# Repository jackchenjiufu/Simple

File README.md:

# Simple Server / DOO

轻量级 PHP RESTful API 服务框架 — 中间件链 + 服务-仓库分层架构，内置 80+ API、频率限制、RBAC 权限、考勤薪资、自动化爬虫、反馈系统。配套 uni-app（Vue 3）跨端 App 和 Vue 3 / 原生双版本管理后台。

## 架构

```
请求 → CORS 中间件 → 日志中间件 → 错误中间件 → 路由 → 响应
                                                    ↓
                                              Service 层
                                                    ↓
                                            Repository 层
                                                    ↓
                                              PDO / MySQL
```

统一路由入口：`/api/*` 经 `.htaccess` → `index.php` 集中分发（RESTful 路由 + 传统文件路由双模式）。

## 目录

```
server/
├── api/          # 80+ API 接口（认证/用户/内容/社交/文件/考勤/反馈/爬虫/管理后台）
├── config/       # Config.php（.env管理） + Database.php（PDO） + RateLimiter.php（限流）
├── middleware/    # CORS / 日志 / 错误 / 认证 — 链式中间件
├── services/     # UserService / ContentService — 业务逻辑
├── repositories/ # UserRepository / ContentRepository — 数据访问
├── uploads/      # 上传文件
├── downloads/    # APK 下载
├── sql/          # 数据库脚本
├── websocket/    # Node.js WebSocket 推送服务（服务端，App 端未接入）
└── mail.php      # 邮件（PHPMailer）

admin-vue/        # 管理后台（Vue 3 SPA，Hash 路由）
admin-web/        # 管理后台（原生 HTML/JS/CSS，传统版）
admin-vue-dist/   # admin-vue 构建产物

pages/            # uni-app (Vue 3) 前端页面
components/       # Vue 组件库
store/            # Vuex 状态管理
utils/            # 工具函数（请求封装/行为分析/缓存）
websocket/        # App 端 WebSocket 连接逻辑（App.vue 内嵌）
```

## 快速开始

```bash
git clone git@github.com:jackchenjiufu/Simple.git
cd Simple
composer install
cp server/config/.env.example server/config/.env   # 编辑数据库配置
mysql -u root -p < server/sql/doo-app.sql
```

```bash
# 初始化
curl http://localhost/server/api/init_database.php
curl http://localhost/server/api/reset_admin.php        # 重置管理员密码（部署后自行设定，勿用示例值）
```

## API 概览（80+ 接口）

| 模块 | 接口数 | 核心功能 |
|------|--------|----------|
| 认证 | 8 | 登录/注册/改密/忘记密码（频率限制 + 邮件验证码） |
| 用户 | 5 | 用户列表/画像/等级/行为分析 |
| 内容 | 10 | CRUD/轮播图/文章/用户行为同步 |
| 反馈 | 2 | 用户提交反馈 + 查看回复历史 |
| 社交 | 6 | 关注/粉丝/私信/聊天记录 |
| 文件/图片 | 11 | 上传/预览/列表/删除/批量导入/下载代理 |
| 收藏 | 2 | 收藏列表/添加收藏 |
| 考勤薪资 | 2 | 打卡 + 加班费 + 五险一金 + 个税（江苏标准） |
| 公告 | 1 | 公告列表 |
| RBAC | 1 | 4 角色 + 12 权限/动态分配 |
| 爬虫 | 3 | 抖音热榜→自动发文章 / picsum→自动发图 |
| 系统 | 9 | 监控/部署/AI代理/版本管理/数据库初始化 |
| 管理后台 | 12 | 用户/内容/轮播/消息/日志/统计/反馈/权限/开屏/文章管理 |

### WebSocket（服务端）

- `websocket/ws-server.js`：Node.js 推送服务（ws://your-domain.com:1884）
- ⚠️ App 端当前**未接入** WebSocket，私聊走轮询（chat.vue 5s / conversations.vue 10s）

## 响应格式

```json
{ "code": 200, "message": "成功", "data": { ... } }
```

## 安全

- bcrypt 密码哈希 | 全量 PDO 预处理 | 频率限制
- Session + Token 双重认证 | CORS 白名单 | 文件上传白名单 + 大小限制
- Token 认证（64 字符随机 hex） | 错误信息脱敏

## 管理后台

| 版本 | 技术 | 路径 | 状态 |
|------|------|------|------|
| Vue 3 SPA | Vue 3 + Vue Router (Hash) | `admin-vue/` | ✅ 主力版 |
| 原生版 | HTML/JS/CSS 传统多页 | `admin-web/` | ✅ 共存 |

功能：仪表盘 / 用户管理 / 内容管理 / 轮播图 / 公告 / 文章 / 反馈管理 / 开屏配置 / 数据统计 / 操作日志

## 技术栈

**后端**: PHP + MySQL + PDO + PHPMailer + Node.js (WebSocket)  
**前端**: uni-app (Vue 3) + Vite + Capacitor 6 → Android APK  
**后台**: Vue 3 SPA + 原生 HTML/JS/CSS 双版本  
**管理入口**: http://your-domain.com:7070/doo/admin-vue/  
**配置**: `E:/poo/doo/server/config/`

## License

ISC

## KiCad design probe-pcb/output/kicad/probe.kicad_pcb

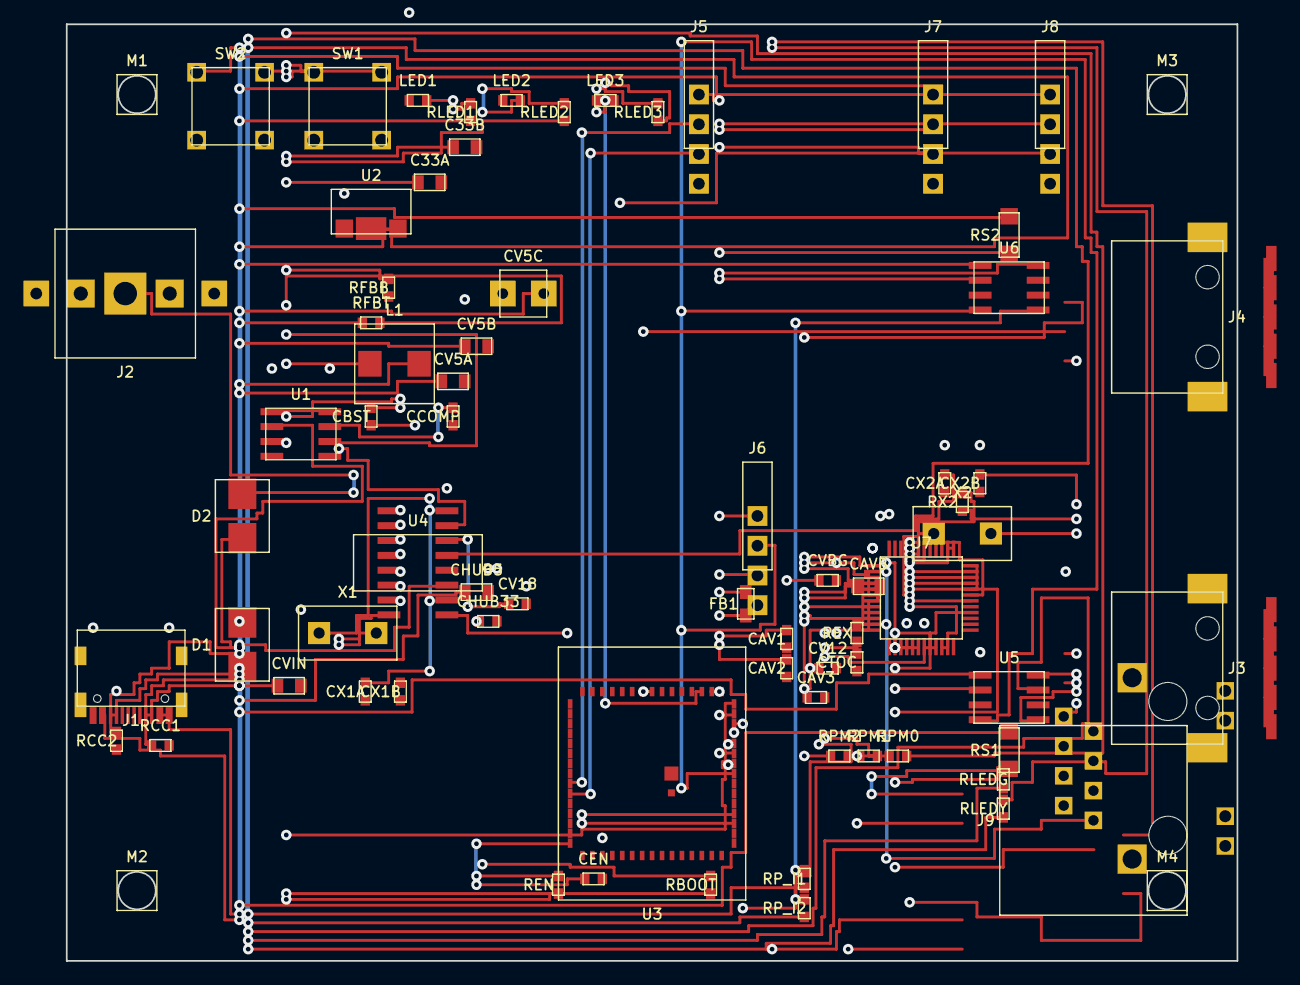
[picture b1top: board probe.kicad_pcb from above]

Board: 2 copper layers, 100.0 x 80.0 mm, 74 parts (0 on the bottom side), 63 nets.

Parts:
C33A: 0805-P; C33A
C33B: 0805-P; C33B
CAV1: 0603-P; CAV1
CAV2: 0603-P; CAV2
CAV3: 0603-P; CAV3
CAVB: 0805-P; CAVB
CBST: 0603-P; CBST
CCOMP: 0603-P; CCOMP
CEN: 0603-P; CEN
CHUB5: 0805-P; CHUB5
CHUB33: 0603-P; CHUB33
CTOC: 0603-P; CTOC
CV5A: 0805-P; CV5A
CV5B: 0805-P; CV5B
CV5C: caprad; CV5C
CV12: 0603-P; CV12
CV18: 0603-P; CV18
CVBG: 0603-P; CVBG
CVIN: 0805-P; CVIN
CX1A: 0603-P; CX1A
CX1B: 0603-P; CX1B
CX2A: 0603-P; CX2A
CX2B: 0603-P; CX2B
D1: SS34; D1
D2: SS34; D2
FB1: FB-0805; FB1
J1: TYPE-C-31-M-12; J1
J2: DC-005; J2
J3: USB3.0-A; J3
J4: USB3.0-A; J4
J5: HDR1x4; J5
J6: HDR1x4; J6
J7: HDR1x4; J7
J8: HDR1x4; J8
J9: HR911105A; J9
L1: 10uH; L1
LED1: LED-0603; LED1
LED2: LED-0603; LED2
LED3: LED-0603; LED3
M1: mount; M1
M2: mount; M2
M3: mount; M3
M4: mount; M4
RBOOT: 0603-P; RBOOT
RCC1: 5.1k; RCC1
RCC2: 5.1k; RCC2
REN: 0603-P; REN
REX: 0603-P; REX
RFBB: 0603-P; RFBB
RFBT: 0603-P; RFBT
RLED1: 0603-P; RLED1
RLED2: 0603-P; RLED2
RLED3: 0603-P; RLED3
RLEDG: 0603-P; RLEDG
RLEDY: 0603-P; RLEDY
RPM0: 0603-P; RPM0
RPM1: 0603-P; RPM1
RPM2: 0603-P; RPM2
RP_I1: 0603-P; RP_I1
RP_I2: 0603-P; RP_I2
RS1: 0.05R; RS1
RS2: 0.05R; RS2
RX2: 0603-P; RX2
SW1: TACT; SW1
SW2: TACT; SW2
U1: MP1584EN; U1
U2: AMS1117-3.3; U2
U3: ESP32-S3-MINI-1; U3
U4: SL2.1A; U4
U5: INA219; U5
U6: INA219; U6
U7: W5500; U7
X1: 12MHz; X1
X2: 25MHz; X2

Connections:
ACTN: J9.10, U7.27
AV33: CAV1.1, CAV2.1, CAV3.1, CAVB.1, FB1.2, U7.4, U7.8, U7.11, U7.15, U7.17, U7.21, U7.28
BOOTN: RBOOT.1, SW2.1, SW2.2, U3.4
BST: CBST.1, U1.1
CC1: J1.A5, RCC1.1
CC2: J1.B5, RCC2.1
COMP: CCOMP.1, U1.7
DC_IN: D2.1, J2.1
ENN: CEN.1, REN.1, SW1.1, SW1.2, U3.45
ETH_RXN: J9.6, U7.5
ETH_RXP: J9.3, U7.6
ETH_TXN: J9.2, U7.1
ETH_TXP: J9.1, U7.2
EXRES: REX.1, U7.10
FB: RFBB.1, RFBT.2, U1.6
GND: C33A.2, C33B.2, CAV1.2, CAV2.2, CAV3.2, CAVB.2, CCOMP.2, CEN.2, CHUB5.2, CHUB33.2, CTOC.2, CV5A.2, CV5B.2, CV5C.-, CV12.2, CV18.2, CVBG.2, CVIN.2, CX1A.2, CX1B.2, CX2A.2, CX2B.2, J1.A1, J1.B1, J1.SH, J2.2, J2.3, J3.4, J3.SH, J4.4, J4.SH, J5.4, J6.4, J7.4, J8.4, J9.SH, LED1.1, RCC1.2, RCC2.2, REX.2, RFBB.2, SW1.3, SW1.4, SW2.3, SW2.4, U1.4, U1.5, U2.1, U3.1, U3.2, U3.42, U3.43, U3.61, U4.12, U5.3, U6.3, U7.3, U7.9, U7.14, U7.16, U7.19, U7.29, U7.48
H1_DM: J3.2, U4.7
H1_DP: J3.3, U4.8
H2_DM: J4.2, U4.5
H2_DP: J4.3, U4.6
H3_DM: J7.2, U4.3
H3_DP: J7.3, U4.4
H4_DM: J8.2, U4.1
H4_DP: J8.3, U4.2
HUB_DM: U3.23, U4.9
HUB_DP: U3.24, U4.10
LED1A: LED1.2, RLED1.1
LED2A: LED2.2, RLED2.1
LED2K: LED2.1, U3.17
LED3A: LED3.2, RLED3.1
LED3K: LED3.1, U3.18
LEDG_A: J9.9, RLEDG.1
LEDY_A: J9.11, RLEDY.1
LINKN: J9.12, U7.25
NC: J1.A6, J1.A7, J1.A8, J1.A9, J1.A12, J1.B6, J1.B7, J1.B8, J1.B9, J1.B12, J2.4, J2.5, J3.5, J3.6, J3.7, J3.8, J3.9, J4.5, J4.6, J4.7, J4.8, J4.9, J9.4, J9.5, J9.7, J9.8, U3.5, U3.6, U3.7, U3.16, U3.19, U3.20, U3.21, U3.22, U3.25, U3.26, U3.27, U3.28, U3.29, U3.30, U3.31, U3.32, U3.33, U3.34, U3.35, U3.36, U3.37, U3.38, U3.41, U3.44, U3.46, U3.47, U3.48, U3.49, U3.50, U3.51, U3.52, U3.53, U3.54, U3.55, U3.56, U3.57, U3.58, U3.59, U3.60, U5.6, U6.6, U7.7, U7.12, U7.13, U7.23, U7.24, U7.26, U7.38, U7.39, U7.40, U7.41, U7.42, U7.46, U7.47
PM0: RPM0.1, U7.45
PM1: RPM1.1, U7.44
PM2: RPM2.1, U7.43
RAW: CVIN.1, D1.2, D2.2, U1.2
RAW_L: D1.1, J1.A4, J1.B4
SCL: J6.2, RP_I1.1, U3.8, U5.4, U6.4
SDA: J6.3, RP_I2.1, U3.9, U5.5, U6.5
SW: CBST.2, L1.1, U1.3
TOCAPN: CTOC.1, U7.20
URX: J5.3, U3.40
UTX: J5.2, U3.39
V5: CHUB5.1, CV5A.1, CV5B.1, CV5C.+, J7.1, J8.1, L1.2, RFBT.1, RLED1.2, RS1.1, RS2.1, U2.3, U4.11, U5.1, U6.1
V12O: CV12.1, U7.22
V18N: CV18.1, U4.14
V33: C33A.1, C33B.1, CHUB33.1, FB1.1, J5.1, J6.1, RBOOT.2, REN.2, RLED2.2, RLED3.2, RLEDG.2, RLEDY.2, RPM0.2, RPM1.2, RPM2.2, RP_I1.2, RP_I2.2, U2.2, U3.3, U4.13, U5.7, U6.7
VBGN: CVBG.1, U7.18
VU1: J3.1, RS1.2, U5.2, U5.8
VU2: J4.1, RS2.2, U6.2, U6.8
W_CS: U3.10, U7.32
W_INT: U3.15, U7.36
W_MISO: U3.13, U7.34
W_MOSI: U3.12, U7.35
W_RST: U3.14, U7.37
W_SCLK: U3.11, U7.33
X1A: CX1A.1, U4.16, X1.1
X1B: CX1B.1, U4.15, X1.2
X2A: CX2A.1, RX2.1, U7.30, X2.1
X2B: CX2B.1, RX2.2, U7.31, X2.2

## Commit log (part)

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2026-06-19 chore: 移除安全审计报告
2026-06-20 add LICENSE.
2026-06-21 fix: 优化文章详情排版、系统设置清理缓存、登录页协议问题、密码重置流程修复
    - 文章详情页排版丰富化，添加封面、作者卡片、标签区、阅读进度
    - 系统设置新增清理缓存功能
    - 登录页移除用户协议复选框（修复无法查看协议问题）
    - 密码重置：邮箱验证码 API 改名绕过 WAF 拦截
    - 修复 PHP 文件 CRLF 换行符导致 404 的问题
    - mail.php 添加 Composer 自动加载 fallback 机制
2026-06-22 v1.2.4: 版本显示修复、密码/重置密码/关于/隐私/协议/设置页面UI统一对齐登录页风格、静默WGT热更新、删除账号功能、检查更新优化
2026-06-22 feat: integrate Getui push notification
    - Add Push module to manifest.json
    - Create push.php API (bind CID / send push)
    - Add push_cid column to users table
    - Initialize push on app launch, auto-bind CID on login
2026-06-22 feat: login auto-bind push CID
2026-06-22 chore: bump to v1.2.5
2026-06-22 feat: push API with Getui integration
2026-06-22 fix: switch to DCloud UniPush API
2026-06-22 fix: WGT热更新改用plus.runtime.install直接传URL下载安装
2026-06-22 Revert "fix: WGT热更新改用plus.runtime.install直接传URL下载安装"
    This reverts commit 758a274cb1e3135793a7abe9cdc422e0af1c9b7e.
2026-06-22 Revert "fix: WGT热更新改用plus.runtime.install直接传URL下载安装"
    This reverts commit a1e476033828624d5a89ebff296d24175be2a5f6.
2026-06-22 v1.2.6: 移除Push模块、修复WGT安装冲突、APK/WGT自动切换、清理硬编码配置
2026-06-23 fix: WebSocket heartbeat 5s, notification API fix
2026-06-23 remove: Getui push integration
2026-06-23 fix: WebSocket reconnect 1s, immediate heartbeat
2026-06-23 fix: use native WebSocket API instead of uni.connectSocket
2026-06-23 fix: simplify WS to uni.connectSocket with heartbeat 10s
2026-06-23 fix: use uni.onSocketOpen/Message/Close global API
2026-06-23 fix: register WS event listeners only once
2026-06-23 fix: WS heartbeat 2s to prevent Android idle timeout
2026-06-23 feat: Node.js WebSocket server (stable replacement for PHP Workerman)
2026-06-23 feat: push API on Node.js WS server
2026-06-23 fix: add Push module back for uni.createPushMessage
2026-06-23 fix: JSON ping/pong heartbeat for uni-app compatibility
2026-06-23 fix: login redirect with no animation to reduce flash
2026-06-23 feat: add splash startup page
2026-06-23 feat: splash config API + admin page
2026-06-23 fix: integrate splash into admin sidebar + script.js
2026-06-23 fix: splash handler in switchMenu
2026-06-27 clean: remove recommend cards, keep carousel only
2026-06-27 fix: syntax error in tabbar-1 methods
2026-06-27 carousel height 300px + adjustable via prop
2026-06-27 carousel default height 300px
2026-06-27 feat: Vue 3 + Element Plus admin backend
2026-06-27 feat: complete admin pages (Announcement/Content/Article/Feedback/Stats/Logs)
2026-06-27 fix: Element Plus icons + axios withCredentials
2026-06-27 fix: admin pages data mapping + session_start fix
2026-06-27 fix: admin pages full data fields + Content/Logs
2026-06-27 feat: add edit/delete for Carousel and Announcement
2026-06-27 feat: Article/Feedback/Dashboard pages + feedback status toggle
2026-06-27 feat: article CRUD + feedback 未读/已读/已解决 + richer dashboard
2026-06-27 feat: user management CRUD (add/edit/delete)
2026-06-27 fix: remove withCredentials (same-origin)
2026-06-27 fix: relative API URL for same-origin
2026-06-27 fix: token-based auth for admin APIs
2026-06-27 fix: auth_helper no body consume + user avatar
2026-06-27 fix: carousel load use GET instead of POST
2026-06-27 fix: delete requests use query params not body
2026-06-27 feat: content CRUD + edit page + dashboard stats
2026-06-27 feat: carousel image upload + user avatar upload
2026-06-27 fix: build errors in carousel upload attributes
2026-06-27 redesign: admin login page (careercompass style)
2026-06-27 redesign: admin-vue login page (careercompass)
2026-06-27 fix: dashboard stats - use real API fields
2026-06-27 fix: live online count from WebSocket server
2026-06-27 feat: feedback history in my-feedback page
2026-06-27 fix: add tab/historyList data
2026-06-27 feat: admin reply to feedback + user sees replies
2026-06-27 feat: feedback history compact list + detail popup
2026-06-27 fix: feedback tab bar styled like top tabs
2026-06-27 fix: accept user_id from POST
